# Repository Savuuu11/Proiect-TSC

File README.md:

# E-book Reader Open-Source
Savu Alin Ion 332CC

### Diagrama

---

### BOM - Bill of Materials

---

| Name of component | Device                                       | Check Prices                                                                                                                                | DataSheet                                                                                                                                   |
|-------------------|----------------------------------------------|---------------------------------------------------------------------------------------------------------------------------------------------|---------------------------------------------------------------------------------------------------------------------------------------------|
| BOOT_BUTTON       | BUTTON_CUSYOMV1                              | [Link](https://industry.panasonic.com/global/en/products/control/switch/light-touch/number/evqpuj02k)                                       | [Link](https://industry.panasonic.com/global/en/products/control/switch/light-touch/number/evqpuj02k)                                       |
| C1                | ESP32_WROVER_EAGLE-LTSPICE_CC0402            | [Link](https://industry.panasonic.com/global/en/products/control/switch/light-touch/number/evqpuj02k)                                       | [Link](https://industry.panasonic.com/global/en/products/control/switch/light-touch/number/evqpuj02k)                                       |
| C1_BAT            | ESP32_WROVER_EAGLE-LTSPICE_CC0402            | #N/A                                                                                                                                        | #N/A                                                                                                                                        |
| C1_BAT1           | EAGLE-LTSPICE_CC0402                         | #N/A                                                                                                                                        | #N/A                                                                                                                                        |
| C1_BAT2           | EAGLE-LTSPICE_CC0402                         | #N/A                                                                                                                                        | #N/A                                                                                                                                        |
| C2                | ESP32_WROVER_EAGLE-LTSPICE_CC0402            | #N/A                                                                                                                                        | #N/A                                                                                                                                        |
| C2_BAT\           | ESP32_WROVER_EAGLE-LTSPICE_CC0402            | #N/A                                                                                                                                        | #N/A                                                                                                                                        |
| C3                | RCL_CPOL-EUCT3528                            | #N/A                                                                                                                                        | #N/A                                                                                                                                        |
| C4                | ESP32_WROVER_EAGLE-LTSPICE_CC0402            | #N/A                                                                                                                                        | #N/A                                                                                                                                        |
| C4_USB            | ESP32_WROVER_EAGLE-LTSPICE_CC0402            | #N/A                                                                                                                                        | #N/A                                                                                                                                        |
| C5                | ESP32_WROVER_EAGLE-LTSPICE_CC0402            | #N/A                                                                                                                                        | #N/A                                                                                                                                        |
| C5_USB            | ESP32_WROVER_EAGLE-LTSPICE_CC0402            | #N/A                                                                                                                                        | #N/A                                                                                                                                        |
| C6                | ESP32_WROVER_EAGLE-LTSPICE_CC0402            | #N/A                                                                                                                                        | #N/A                                                                                                                                        |
| C7                | ESP32_WROVER_EAGLE-LTSPICE_CC0402            | #N/A                                                                                                                                        | #N/A                                                                                                                                        |
| C8                | ESP32_WROVER_EAGLE-LTSPICE_CC0402            | #N/A                                                                                                                                        | #N/A                                                                                                                                        |
| C9                | EAGLE-LTSPICE_CC0402                         | #N/A                                                                                                                                        | #N/A                                                                                                                                        |
| C10               | ESP32_WROVER_EAGLE-LTSPICE_CC0402            | #N/A                                                                                                                                        | #N/A                                                                                                                                        |
| C10_SUPERCAP      | CPH3225A                                     | [Link](https://www.snapeda.com/parts/CPH3225A/Seiko+Instruments/view-part/?ref=eda)                                                          | [Link](https://www.snapeda.com/parts/CPH3225A/Seiko+Instruments/view-part/?ref=eda)                                                          |
| CHANGE_BUTTON     | BUTTON_CUSYOMV1                              | [Link](https://industry.panasonic.com/global/en/products/control/switch-light-touch/number/evqpuj02k)                                       | [Link](https://industry.panasonic.com/global/en/products/control/switch-light-touch/number/evqpuj02k)                                       |
| CHG_LED           | ADAFRUIT_LEDCHIP-LED0603                     | [Link](https://www.snapeda.com/parts/KP-1608SURCK/Kingbright/view-part/?ref=search&t=LED%200603)                                             | [Link](https://www.snapeda.com/parts/KP-1608SURCK/Kingbright/view-part/?ref=search&t=LED%200603)                                             |
| C_DELAY           | ESP32_WROVER_EAGLE-LTSPICE_CC0402            | #N/A                                                                                                                                        | #N/A                                                                                                                                        |
| D1                | USBLC6-2SC6Y                                 | [Link](https://www.snapeda.com/parts/USBLC6-2SC6Y/STMicroelectronics/view-part/?ref=eda)                                                    | [Link](https://www.snapeda.com/parts/USBLC6-2SC6Y/STMicroelectronics/view-part/?ref=eda)                                                    |
| D2                | ESP32_WROVER_AVX---SD0805S020S1R0_AVX_...    | [Link](https://eu.mouser.com/ProductDetail/KYOCERA-AVX/SD0805S020S1R0?qs=jCA%252BPfw4LHbpkAoSnwrdjw%3D%3D)                                    | [Link](http://datasheets.avx.com/schottky.pdf)                                                                                              |
| D3                | MBR0530                                      | [Link](https://eu.mouser.com/ProductDetail/KYOCERA-AVX/SD0805S020S1R0?qs=jCA%252BPfw4LHbpkAoSnwrdjw%3D%3D)                                    | [Link](https://eu.mouser.com/ProductDetail/KYOCERA-AVX/SD0805S020S1R0?qs=jCA%252BPfw4LHbpkAoSnwrdjw%3D%3D)                                    |
| D4                | MBR0530                                      | [Link](https://www.snapeda.com/parts/MBR0530/Onsemi/view-part/?ref=eda)                                                                     | [Link](https://www.snapeda.com/parts/MBR0530/Onsemi/view-part/?ref=eda)                                                                     |
| D5                | MBR0530                                      | [Link](https://www.snapeda.com/parts/MBR0530/Onsemi/view-part/?ref=eda)                                                                     | [Link](https://www.snapeda.com/parts/MBR0530/Onsemi/view-part/?ref=eda)                                                                     |
| D6                | PGB1010603MR                                 | [Link](https://www.snapeda.com/parts/PGB1010603MR/Littelfuse/view-part/?ref=eda)                                                            | [Link](https://www.snapeda.com/parts/PGB1010603MR/Littelfuse/view-part/?ref=eda)                                                            |
| D7                | ESP32_WROVER_AVX---SD0805S020S1R0_AVX_...    | [Link](https://eu.mouser.com/ProductDetail/KYOCERA-AVX/SD0805S020S1R0?qs=jCA%252BPfw4LHbpkAoSnwrdjw%3D%3D)                                    | [Link](http://datasheets.avx.com/schottky.pdf)                                                                                              |
| D8                | PGB1010603MR                                 | [Link](https://www.snapeda.com/parts/PGB1010603MR/Littelfuse/view-part/?ref=eda)                                                            | [Link](https://www.snapeda.com/parts/PGB1010603MR/Littelfuse/view-part/?ref=eda)                                                            |
| D9                | PGB1010603MR                                 | [Link](https://www.snapeda.com/parts/PGB1010603MR/Littelfuse/view-part/?ref=eda)                                                            | [Link](https://www.snapeda.com/parts/PGB1010603MR/Littelfuse/view-part/?ref=eda)                                                            |
| D10               | PGB1010603MR                                 | [Link](https://www.snapeda.com/parts/PGB1010603MR/Littelfuse/view-part/?ref=eda)                                                            | [Link](https://www.snapeda.com/parts/PGB1010603MR/Littelfuse/view-part/?ref=eda)                                                            |
| D11               | PGB1010603MR                                 | [Link](https://www.snapeda.com/parts/PGB1010603MR/Littelfuse/view-part/?ref=eda)                                                            | [Link](https://www.snapeda.com/parts/PGB1010603MR/Littelfuse/view-part/?ref=eda)                                                            |
| D12               | PGB1010603MR                                 | [Link](https://www.snapeda.com/parts/PGB1010603MR/Littelfuse/view-part/?ref=eda)                                                            | [Link](https://www.snapeda.com/parts/PGB1010603MR/Littelfuse/view-part/?ref=eda)                                                            |
| EPD_C1            | ESP32_WROVER_EAGLE-LTSPICE_CC0402            | #N/A                                                                                                                                        | #N/A                                                                                                                                        |
| EPD_C2            | ESP32_WROVER_EAGLE-LTSPICE_CC0402            | #N/A                                                                                                                                        | #N/A                                                                                                                                        |
| EPD_C5            | ESP32_WROVER_EAGLE-LTSPICE_CC0402            | #N/A                                                                                                                                        | #N/A                                                                                                                                        |
| EPD_C6            | ESP32_WROVER_EAGLE-LTSPICE_CC0402            | #N/A                                                                                                                                        | #N/A                                                                                                                                        |
| EPD_C7            | ESP32_WROVER_EAGLE-LTSPICE_CC0402            | #N/A                                                                                                                                        | #N/A                                                                                                                                        |
| EPD_C8            | ESP32_WROVER_EAGLE-LTSPICE_CC0402            | #N/A                                                                                                                                        | #N/A                                                                                                                                        |
| EPD_C9            | ESP32_WROVER_EAGLE-LTSPICE_CC0402            | #N/A                                                                                                                                        | #N/A                                                                                                                                        |
| EPD_C10           | ESP32_WROVER_EAGLE-LTSPICE_CC0402            | #N/A                                                                                                                                        | #N/A                                                                                                                                        |
| EPD_C11           | ESP32_WROVER_EAGLE-LTSPICE_CC0402            | #N/A                                                                                                                                        | #N/A                                                                                                                                        |
| EPD_C12           | ESP32_WROVER_EAGLE-LTSPICE_CC0402            | #N/A                                                                                                                                        | #N/A                                                                                                                                        |
| IC1               | BD5229G-TR                                   | [Link](https://componentsearchengine.com/part-view/BD5229G-TR/ROHM%20Semiconductor)                                                         | [Link](https://componentsearchengine.com/part-view/BD5229G-TR/ROHM%20Semiconductor)                                                         |
| IC4               | XC6220A331MR-G                               | [Link](https://componentsearchengine.com/part-view/XC6220A331MR-G/Torex)                                                                     | [Link](https://componentsearchengine.com/part-view/XC6220A331MR-G/Torex)                                                                     |
| J1                | FH34SRJ-24S-0.5SH_99_                        | [Link](https://componentsearchengine.com/part-view/XC6220A331MR-G/Torex)                                                                     | [Link](https://componentsearchengine.com/part-view/XC6220A331MR-G/Torex)                                                                     |
| J2                | SAMACSYS_PARTS_USB4110-GF-A                  | [Link](https://componentsearchengine.com/part-view/USB4110-GF-A/GCT%20(GLOBAL%20CONNECTOR%20TECHNOLOGY)                                      | [Link](https://componentsearchengine.com/part-view/USB4110-GF-A/GCT%20(GLOBAL%20CONNECTOR%20TECHNOLOGY)                                      |
| J3                | QWIIC_CONNECTORJS-1MM                        | #N/A                                                                                                                                        | #N/A                                                                                                                                        |
| J4                | 112A-TAAR-R03_ATTEND                         | [Link](https://store.comet.srl.ro/Catalogue/Product/43497/)                                                                                | [Link](https://store.comet.srl.ro/Catalogue/Product/43497/)                                                                                |
| L1                | 744043680IND_4828-WE-TPC_WRE                 | [Link](https://eu.mouser.com/ProductDetail/Wurth-Elektronik/744043680?qs=PGXP4M47uW6VkZq%252BkzjrHA%3D%3D)                                    | [Link](https://eu.mouser.com/ProductDetail/Wurth-Elektronik/744043680?qs=PGXP4M47uW6VkZq%252BkzjrHA%3D%3D)                                    |
| PFMF.050.1        | ESP32C6_VARISTORCN1812                       | [Link](https://www.mouser.co.uk/ProductDetail/EPCOS-TDK/B72520T0350K062?qs=dEfas%2FXlABIszF52uu7vrg%3D%3D)                                  | [Link](https://www.mouser.co.uk/ProductDetail/EPCOS-TDK/B72520T0350K062?qs=dEfas%2FXlABIszF52uu7vrg%3D%3D)                                  |
| Q1                | ESP32_WROVER_SPARKFUN-DISCRETESEMI_MOSFET_...| [Link](https://componentsearchengine.com/part-view/DMG2305UX-7/Diodes%20Incorporated)                                                       | [Link](https://componentsearchengine.com/part-view/DMG2305UX-7/Diodes%20Incorporated)                                                       |
| Q2                | ESP32_WROVER_SPARKFUN-DISCRETESEMI_MOSFET_...| #N/A                                                                                                                                        | #N/A                                                                                                                                        |
| Q3                | D8                                           | [Link](https://componentsearchengine.com/part-view/SI1308EDL-T1-GE3/Vishay)                                                                 | [Link](https://componentsearchengine.com/part-view/SI1308EDL-T1-GE3/Vishay)                                                                 |
| R1                | ESP32_WROVER_EAGLE-LTSPICE_RR0402            | #N/A                                                                                                                                        | #N/A                                                                                                                                        |
| R1-PINH           | ESP32_WROVER_EAGLE-LTSPICE_RR0402            | #N/A                                                                                                                                        | #N/A                                                                                                                                        |
| R1-PINH1          | ESP32_WROVER_EAGLE-LTSPICE_RR0402            | #N/A                                                                                                                                        | #N/A                                                                                                                                        |
| R1_BAT            | ESP32_WROVER_EAGLE-LTSPICE_RR0402            | #N/A                                                                                                                                        | #N/A                                                                                                                                        |
| R1_PWRUSB         | ESP32_WROVER_EAGLE-LTSPICE_RR0402            | #N/A                                                                                                                                        | #N/A                                                                                                                                        |
| R2                | ESP32_WROVER_EAGLE-LTSPICE_RR0402            | [Link](https://componentsearchengine.com/part-view/R0402%201%25%20100%20K%20(RC0402FR-07100KL)                                               | [Link](https://componentsearchengine.com/part-view/R0402%201%25%20100%20K%20(RC0402FR-07100KL)                                               |
| R2-PINH           | ESP32_WROVER_EAGLE-LTSPICE_RR0402            | #N/A                                                                                                                                        | #N/A                                                                                                                                        |
| R2-PINH1          | ESP32_WROVER_EAGLE-LTSPICE_RR0402            | #N/A                                                                                                                                        | #N/A                                                                                                                                        |
| R2-USB            | ESP32_WROVER_EAGLE-LTSPICE_RR0402            | #N/A                                                                                                                                        | #N/A                                                                                                                                        |
| R2-USB1           | ESP32_WROVER_EAGLE-LTSPICE_RR0402            | #N/A                                                                                                                                        | #N/A                                                                                                                                        |
| R2_BAT            | ESP32_WROVER_EAGLE-LTSPICE_RR0402            | #N/A                                                                                                                                        | #N/A                                                                                                                                        |
| R3                | ESP32_WROVER_EAGLE-LTSPICE_RR0402            | #N/A                                                                                                                                        | #N/A                                                                                                                                        |
| R4                | ESP32_WROVER_EAGLE-LTSPICE_RR0402            | #N/A                                                                                                                                        | #N/A                                                                                                                                        |
| R5                | ESP32_WROVER_EAGLE-LTSPICE_RR0402            | #N/A                                                                                                                                        | #N/A                                                                                                                                        |
| R6                | ESP32_WROVER_EAGLE-LTSPICE_RR0402            | #N/A                                                                                                                                        | #N/A                                                                                                                                        |
| R7                | ESP32_WROVER_EAGLE-LTSPICE_RR0402            | #N/A                                                                                                                                        | #N/A                                                                                                                                        |
| R8                | ESP32_WROVER_EAGLE-LTSPICE_RR0402            | #N/A                                                                                                                                        | #N/A                                                                                                                                        |
| R9                | ESP32_WROVER_EAGLE-LTSPICE_RR0402            | #N/A                                                                                                                                        | #N/A                                                                                                                                        |
| R10               | ESP32_WROVER_EAGLE-LTSPICE_RR0402            | #N/A                                                                                                                                        | #N/A                                                                                                                                        |
| RESET_BUTTON      | BUTTON_CUSYOMV1                              | [Link](https://industry.panasonic.com/global/en/products/control/switch/light-touch/number/evqpuj02k)                                       | [Link](https://industry.panasonic.com/global/en/products/control/switch/light-touch/number/evqpuj02k)                                       |
| R_BOOT            | ESP32_WROVER_EAGLE-LTSPICE_RR0402            | #N/A                                                                                                                                        | #N/A                                                                                                                                        |
| R_CAPACITOR       | ESP32_WROVER_EAGLE-LTSPICE_RR0402            | #N/A                                                                                                                                        | #N/A                                                                                                                                        |
| R_CHANGE          | ESP32_WROVER_EAGLE-LTSPICE_RR0402            | #N/A                                                                                                                                        | #N/A                                                                                                                                        |
| R_CL1             | ESP32_WROVER_EAGLE-LTSPICE_RR0402            | #N/A                                                                                                                                        | #N/A                                                                                                                                        |
| R_RESET           | ESP32_WROVER_EAGLE-LTSPICE_RR0402            | #N/A                                                                                                                                        | #N/A                                                                                                                                        |
| SENSOR2           | ESP32_WROVER_BME680_BME680                   | [Link](https://www.snapeda.com/parts/BME680/Bosch/view-part/?welcome=home)                                                                  | [Link](https://www.snapeda.com/parts/BME680/Bosch/view-part/?welcome=home)                                                                  |
| SJ1               | SJ                                           | [Link](https://grabcad.com/library/solder-jumpers-1)                                                                                        | [Link](https://grabcad.com/library/solder-jumpers-1)                                                                                        |
| TP1               | TPTP20R                                      | #N/A                                                                                                                                        | #N/A                                                                                                                                        |
| TP2               | TPTP20R                                      | #N/A                                                                                                                                        | #N/A                                                                                                                                        |
| TP3               | TPTP20R                                      | #N/A                                                                                                                                        | #N/A                                                                                                                                        |
| TP4               | TPTP20R                                      | #N/A                                                                                                                                        | #N/A                                                                                                                                        |
| TP5               | TPTP20R                                      | #N/A                                                                                                                                        | #N/A                                                                                                                                        |
| TP6               | TPTP20R                                      | #N/A                                                                                                                                        | #N/A                                                                                                                                        |
| TP7               | TPTP20R                                      | #N/A                                                                                                                                        | #N/A                                                                                                                                        |
| TP8               | TPTP20R                                      | #N/A                                                                                                                                        | #N/A                                                                                                                                        |
| TP9               | TPTP20R                                      | #N/A                                                                                                                                        | #N/A                                                                                                                                        |
| TP10              | TPTP20R                                      | #N/A                                                                                                                                        | #N/A                                                                                                                                        |
| TP11              | TPTP20R                                      | #N/A                                                                                                                                        | #N/A                                                                                                                                        |
| TP12              | TPTP20R                                      | #N/A                                                                                                                                        | #N/A                                                                                                                                        |
| TP13              | TPTP20R                                      | #N/A                                                                                                                                        | #N/A                                                                                                                                        |
| TP14              | TPTP20R                                      | #N/A                                                                                                                                        | #N/A                                                                                                                                        |
| TP15              | TPTP20R                                      | #N/A                                                                                                                                        | #N/A                                                                                                                                        |
| TP16              | TPTP20R                                      | #N/A                                                                                                                                        | #N/A                                                                                                                                        |
| TP17              | TPTP20R                                      | #N/A                                                                                                                                        | #N/A                                                                                                                                        |
| U1                | W25Q512JVEIQ                                 | [Link](https://www.snapeda.com/parts/W25Q512JVEIQ/Winbond+Electronics/view-part/?ref=eda)                                                    | [Link](https://www.snapeda.com/parts/W25Q512JVEIQ/Winbond+Electronics/view-part/?ref=eda)                                                    |
| U2                | ESP32-C6-WROOM-1-N8                          | [Link](https://www.snapeda.com/parts/ESP32-C6-WROOM-1-N8/Espressif+Systems/view-part/?ref=eda)                                              | [Link](https://www.snapeda.com/parts/ESP32-C6-WROOM-1-N8/Espressif+Systems/view-part/?ref=eda)                                              |
| U3                | DS3231SN#                                    | [Link](https://www.snapeda.com/parts/DS3231SN%23/Analog+Devices/view-part/?ref=eda)                                                         | [Link](https://www.snapeda.com/parts/DS3231SN%23/Analog+Devices/view-part/?ref=eda)                                                         |
| U4                | MAX17048G+T10                                | [Link](https://www.snapeda.com/parts/MAX17048G+T10/Analog+Devices/view-part/?ref=eda)                                                       | [Link](https://www.snapeda.com/parts/MAX17048G+T10/Analog+Devices/view-part/?ref=eda)                                                       |
| U5                | ESP32_WROVER_SPARKFUN-IC-POWER_MCP73831      | [Link](https://eu.mouser.com/ProductDetail/Microchip-Technology/MCP73831T-2ACI-OT?qs=yUQqVecv4qvbBQBGbHx0Mw%3D%3Dcf)                         | [Link](https://eu.mouser.com/ProductDetail/Microchip-Technology/MCP73831T-2ACI-OT?qs=yUQqVecv4qvbBQBGbHx0Mw%3D%3Dcf)                         |

## Descriere Funcționalități Hardware

---

## 1. Unitate de Control – ESP32-C6  
- **Microcontroller**: `ESP32-C6-WROOM-1` (32-bit RISC-V @ 160 MHz)  
- **Memorie**:  
  - 512 KB SRAM integrat pentru procesare rapidă.  
  - 8 MB flash extern (`W25Q512JVEIQ`) pentru stocare persistentă.  
- **Conectivitate**:  
  - Wi-Fi 6 (802.11ax), Bluetooth Low Energy 5.  
  - Port USB 2.0 (full-speed).  
- **Periferice**:  
  - SPI, I²C, UART.  
  - 22 de pini GPIO configurabili.  
- **Eficiență energetică**:  
  - Moduri `sleep` și `deep sleep` (<10µA).  

---

## 2. Afișaj E-Ink (7.5 inch)  
- **Model**: Waveshare 800×480 px.  
- **Interfață**:  
  - SPI 4-fire (CS, DC, RST, BUSY).  
- **Consum energie**:  
  - **0W** în stare statică.  
  - Vârf de **25mA** la actualizare.  
- **Beneficiu**:  
  - Imagine persistentă fără alimentare.  

---

## 3. Senzor Multi-Parametru – BME680  
- **Măsurători**:  
  - Temperatură (±0.5°C), umiditate (±3%), presiune atmosferică, VOC.  
- **Interfață**: I²C @ 400 kHz.  
- **Consum**:  
  - 2.1µA în standby, 3.7mA în activitate.  
- **Avantaj**: Integrare 4-în-1 într-un singur cip.  

---

## 4. Sistem de Management al Energiei  
- **Baterie**: Li-Po 2500mAh (3.7V).  
- **Încărcare**:  
  - Controler `MCP73831` (1A via USB-C).  
- **Monitorizare**:  
  - `MAX17048` pentru nivel încărcare, tensiune și alertă.  
- **Regulator LDO**:  
  - `XC6220A331MR-G` (3.3V stabil).  

---

## 5. Interfață Utilizator – Butoane Tactile  
- **3 butoane** pentru navigare, selecție și control.  
- **Debouncing**:  
  - Hardware (circuite RC) sau software.  

---

## 6. Port USB-C  
- **Funcții**:  
  - Încărcare baterie și transfer date.  
- **Protecție**:  
  - Diodă ESD `USBLC6-2SC6Y`.  

---

## 7. Conector Qwiic pentru Expansiune  
- **4 pini standard**: VCC, GND, SDA, SCL.  
- **Scop**: Conectare senzori I²C externi (ex: senzor de lumină).  

---

## 8. Slot MicroSD  
- **Conector**: `112A-TAAR-R03`.  
- **Capacitate**: Suportă carduri microSD (stocare e-book-uri/log-uri).  
- **Interfață**: Configurabilă SPI/SD.  

---

## 9. Ceas Real-Time (DS3231)  
- **Precizie**: ±2ppm.  
- **Backup**: Supercondensator/baterie secundară.  

---

## 10. Memorie Flash Externă  
- **Model**: `W25Q512JVEIQ`.  
- **Interfață**: Quad SPI (133 MHz).  
- **Utilizare**: Firmware, setări, conținut utilizator.  

--- 

### 🔌 Interfețe și Alocare Resurse  

#### **Interfețe Utilizate**  
| Protocol | Componente Conectate               |  
|----------|------------------------------------|  
| **SPI**  | E-Paper, Memorie Flash, Card SD    |  
| **I²C**  | BME680, MAX17048, DS3231, Qwiic    |  
| **GPIO** | Butoane, Semnale Control E-Paper   |  
| **USB**  | Alimentare + Transfer Date (USB-C) |  

---

#### **Estimare Autonomie Baterie**  
| Componentă             | Consum (Activ) | Consum (Standby) |  
|------------------------|----------------|------------------|  
| **ESP32-C6**           | 80 mA          | <10 µA           |  
| **E-Paper (refresh)**  | 25 mA          | 0 mA             |  
| **BME680**             | 3.6 mA         | 2.1 µA           |  
| **MAX17048**           | -              | 50 µA            |  
| **DS3231**             | 3.5 mA         | <1 µA            |  
| **Total**              | ~150 mA        | ~100 µA          |  

---

#### **Mapare Pini ESP32-C6**  
| Pin   | Funcție Principală                 | Detalii                          |  
|-------|------------------------------------|----------------------------------|  
| GPIO1 | I²C SDA                            | Senzori BME680, MAX17048, DS3231 |  
| GPIO2 | I²C SCL                            | Clock pentru magistrala I²C      |  
| GPIO5 | SPI MISO (E-Paper)                 | Recepție date afișaj             |  
| GPIO6 | SPI MOSI (E-Paper)                 | Transmitere date afișaj          |  
| GPIO7 | SPI CLK (E-Paper)                  | Semnal ceas SPI                  |  
| GPIO8 | SPI CS (E-Paper)                   | Selectare chip afișaj            |  
| GPIO9 | DC (E-Paper)                       | Comutare date/comenzi            |  
| GPIO10| RST (E-Paper)                      | Reset hardware afișaj            |  
| GPIO11| BUSY (E-Paper)                     | Indică ocupare afișaj            |  
| GPIO12| Buton #1                           | Navigare "Pagina Următoare"      |  
| GPIO13| Buton #2                           | Navigare "Pagina Anterioară"     |  
| GPIO14| Buton #3                           | Meniu/Selectare                  |  
| GPIO15| ALERT (MAX17048)                   | Avertizare baterie scăzută       |  
| GPIO19| SD Card CS                         | Selectare card MicroSD           |  

---

### Conluzii
A fost un proiect foarte muncitoresc, care merita mai mult decat 2 pct.
Timp de lucru: 70h

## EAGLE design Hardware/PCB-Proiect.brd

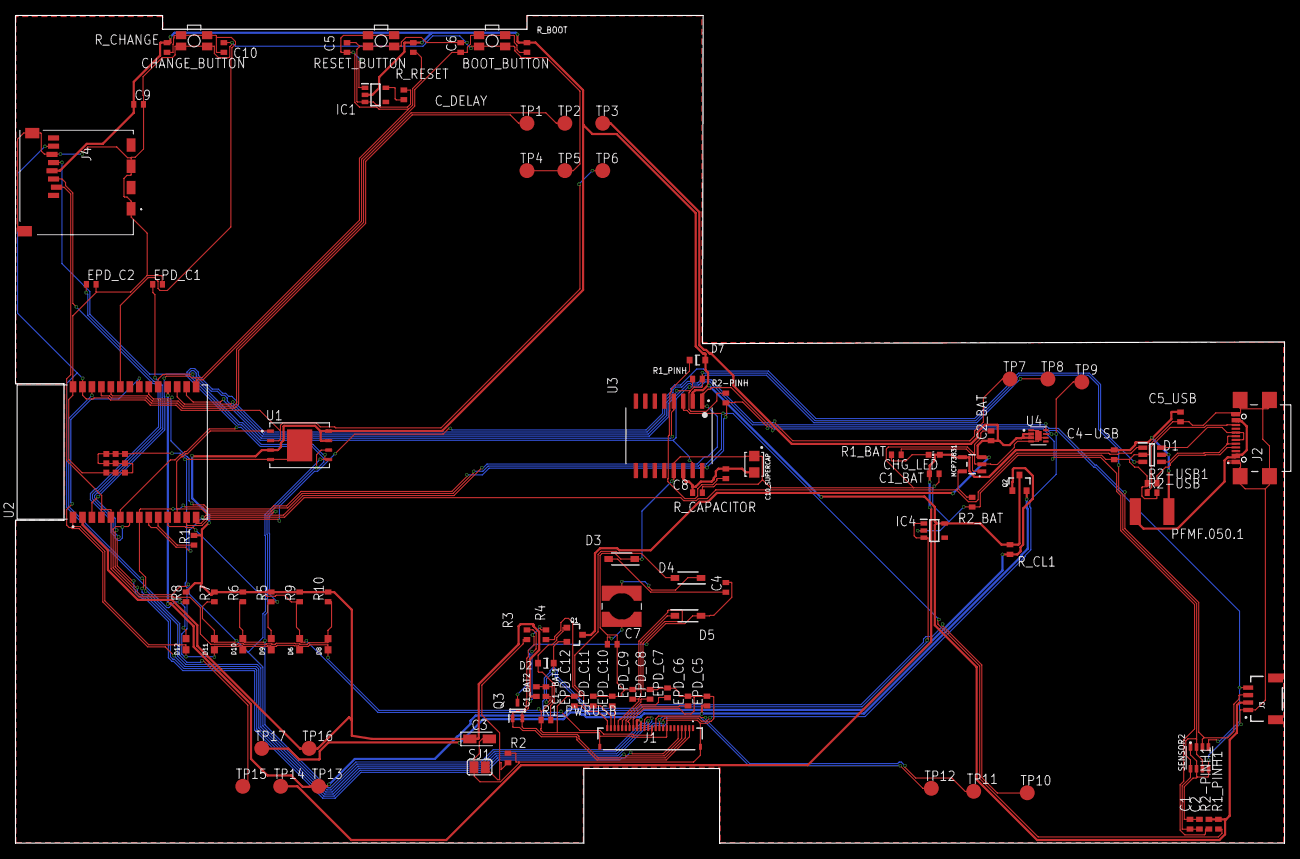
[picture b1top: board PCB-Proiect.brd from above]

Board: 2 copper layers, 170.2 x 111.0 mm, 103 parts (0 on the bottom side), 58 nets.

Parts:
BOOT_BUTTON: BUTTON_CUSYOMV1; MYBUTTON
C1, C2, C6, C8, C9, C10: 100nF; EAGLE-LTSPICE_C0402
C1-BAT1, C1_BAT2, C5_USB: 4.7uF; ESP32_WROVER_EAGLE-LTSPICE_C0402
C1_BAT, C2_BAT: 4.7uF; EAGLE-LTSPICE_C0402
C3: 100uF TANT; CAPMP3216X180N
C4: 4.7uF/25V; EAGLE-LTSPICE_C0402
C4-USB: 100nF; ESP32_WROVER_EAGLE-LTSPICE_C0402
C5: 1uF; EAGLE-LTSPICE_C0402
C7: 10uF; EAGLE-LTSPICE_C0402
C10_SUPERCAP: CPH3225A; CAPCP3225X100N
CHANGE_BUTTON: BUTTON_CUSYOMV1; MYBUTTON
CHG_LED: ADAFRUIT_CHIP-LED0603
C_DELAY: 100nF; EAGLE-LTSPICE_C0402
D1: USBLC6-2SC6Y; SOT95P280X145-6N
D2, D7: ESP32_WROVER_AVX---SD0805S020S1R0_AVX_SD0805S020S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; ESP32_WROVER_AVX---SD0805S020S1R0_AVX_SD0805S020S1R0_0
D3, D4, D5: MBR0530; SOD3716X135N
D6, D8, D9, D10, D11, D12: PGB1010603MR; DIOC1608X36N
EPD_C1, EPD_C2, EPD_C5, EPD_C6, EPD_C7, EPD_C8, EPD_C9, EPD_C10, EPD_C11, EPD_C12: 1uF/50V; EAGLE-LTSPICE_C0402
IC1: BD5229G-TR; SOT95P280X125-5N
IC4: XC6220A331MR-G; SOT95P280X120-5N
J1: FH34SRJ-24S-0.5SH_99_; FH34SRJ24S05SH99
J2: SAMACSYS_PARTS_USB4110-GF-A; SAMACSYS_PARTS_USB4110GFA
J3: QWIIC_RIGHT_ANGLE; JST04_1MM_RA
J4: 112A-TAAR-R03_ATTEND; 112ATAARR03ATTEND
L1: 68uH; IND_4828-WE-TPC_WRE
MCP73831: ESP32_WROVER_SPARKFUN-IC-POWER_MCP73831; ESP32_WROVER_SPARKFUN-IC-POWER_SOT23-5
PFMF.050.1: ESP32C6_VARISTORCN1812; ESP32C6_VARISTOR_CT/CN1812
Q1, Q2: 20V/4.2A/52mΩ/1.4W; ESP32_WROVER_SPARKFUN-DISCRETESEMI_SOT23-3
Q3: SI1308EDL-T1-GE3; SOT65P210X110-3N
R1, R1_PINH, R1_PINH1, R2-PINH, R2-PINH1, R4, R5, R6, R7, R8, R9, R10: 10K; ESP32_WROVER_EAGLE-LTSPICE_R0402
R1_BAT: 200; ESP32_WROVER_EAGLE-LTSPICE_R0402
R1_PWRUSB: 100K; ESP32_WROVER_EAGLE-LTSPICE_R0402
R2: 2.2; ESP32_WROVER_EAGLE-LTSPICE_R0402
R2-USB, R2-USB1: 5k1; ESP32_WROVER_EAGLE-LTSPICE_R0402
R2_BAT: 2K; ESP32_WROVER_EAGLE-LTSPICE_R0402
R3: 0.47; ESP32_WROVER_EAGLE-LTSPICE_R0402
RESET_BUTTON: BUTTON_CUSYOMV1; MYBUTTON
R_BOOT: 10K; ESP32_WROVER_EAGLE-LTSPICE_R0402
R_CAPACITOR: 15; ESP32_WROVER_EAGLE-LTSPICE_R0402
R_CHANGE: 10K; ESP32_WROVER_EAGLE-LTSPICE_R0402
R_CL1: 10K; ESP32_WROVER_EAGLE-LTSPICE_R0402
R_RESET: 10K; ESP32_WROVER_EAGLE-LTSPICE_R0402
SENSOR2: ESP32_WROVER_BME680_BME680; ESP32_WROVER_BME680_PSON80P300X300X100-8N
SJ1: SJ
TP1, TP2, TP3, TP4, TP5, TP6, TP7, TP8, TP9, TP10, TP11, TP12, TP13, TP14, TP15, TP16, TP17: TPTP20R; TP20R
U1: W25Q512JVEIQ; SON127P600X800X80-9N
U2: ESP32-C6-WROOM-1-N8; XCVR_ESP32-C6-WROOM-1-N8
U3: DS3231SN#; SOIC127P1032X265-16N
U4: MAX17048G+T10; SON50P200X200X80-9N

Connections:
3V3: C1_BAT2.1, C3.1, C9.1, D7.2, IC1.2, IC4.5, J3.2, J4.P4, Q2.3, R1.2, R1_PINH1.2, R2-PINH1.2, R5.2, R6.2, R7.2, R8.2, R9.2, R10.2, R_BOOT.2, R_CHANGE.2, R_CL1.2, R_RESET.2, TP16.TP, U1.3, U1.7, U1.8, U2.2, U3.2
32KHZ: R2-PINH1.1, U2.9, U3.1
DN: D1.4, J2.A7, J2.B7
DP: D1.6, J2.A6, J2.B6
EPD_3V3: EPD_C5.1, J1.15, J1.16, Q2.2, TP17.TP
EPD_3V3_C: Q2.1, R_CL1.1, TP13.TP, U2.18
EPD_BUSY: J1.9, TP9.TP, U2.26
EPD_CS: D6.2, J1.12, R9.1, TP10.TP, U2.11
EPD_DC: J1.11, TP11.TP
EPD_RST: J1.10, TP12.TP, U2.21
FLASH_CS: D9.2, R5.1, U1.1, U2.12
GDR: J1.2, Q3.1, R4.2
GND: BOOT_BUTTON.1, BOOT_BUTTON.2, C1.2, C1-BAT1.2, C1_BAT.2, C1_BAT2.2, C2.2, C2_BAT.2, C3.2, C4-USB.1, C5.2, C5_USB.1, C6.2, C7.2, C8.2, C9.2, C10.2, C10_SUPERCAP.1, CHANGE_BUTTON.1, CHANGE_BUTTON.2, C_DELAY.2, D1.2, D3.1, D6.1, D8.1, D9.1, D10.1, D11.1, D12.1, EPD_C1.2, EPD_C2.2, EPD_C5.2, EPD_C6.2, EPD_C7.2, EPD_C8.2, EPD_C9.2, EPD_C10.2, EPD_C11.2, EPD_C12.2, IC1.3, IC4.2, J1.8, J1.17, J1.MP1, J1.MP2, J2.A1, J2.A12, J2.B1, J2.B12, J2.MP1, J2.MP2, J2.MP3, J2.MP4, J3.1, J4.G1, J4.G2, J4.G3, J4.G4, J4.P6, MCP73831.2, R1_PWRUSB.1, R2.2, R2-USB.2, R2-USB1.1, R2_BAT.1, R4.1, RESET_BUTTON.1, RESET_BUTTON.2, SENSOR2.1, SENSOR2.5, SENSOR2.7, SJ1.1, TP4.TP, TP5.TP, U1.4, U1.9, U2.1, U2.28, U2.29_1, U2.29_2, U2.29_3, U2.29_4, U2.29_5, U2.29_6, U2.29_7, U2.29_8, U2.29_9, U3.13, U4.1, U4.4, U4.6, U4.9
GPI08: R1.1, U2.10
I2C_PW: C1.1, C2.1, R1_PINH.2, R2-PINH.2, SENSOR2.2, SENSOR2.6, SENSOR2.8, U2.17
INT_RTC: R1_PINH1.1, TP15.TP, U2.8, U3.3
IO/BOOT: BOOT_BUTTON.3, BOOT_BUTTON.4, C6.1, R_BOOT.1, U2.15
IO/CHANGE: C10.1, CHANGE_BUTTON.3, CHANGE_BUTTON.4, R_CHANGE.1, U2.23
MISO: D12.2, J4.P7, R8.1, TP6.TP, U1.2, U2.27
MOSI: D11.2, J1.14, J4.P3, R7.1, TP7.TP, U1.5, U2.7
unnamed: D2.2, Q1.1, R1_PWRUSB.2
unnamed: J2.B5, R2-USB.1
unnamed: J2.A5, R2-USB1.2
unnamed: C7.1, L1.2
unnamed: C1-BAT1.1, D2.1, IC4.1, IC4.3, Q1.2
unnamed: D4.1, L1.1
unnamed: C4.1, D3.2
unnamed: CHG_LED.C, R1_BAT.1
unnamed: MCP73831.1, R1_BAT.2
unnamed: MCP73831.5, R2_BAT.2
unnamed: C_DELAY.1, IC1.5
unnamed: EPD_C12.1, J1.24
unnamed: EPD_C10.1, J1.22
unnamed: EPD_C8.1, J1.20
unnamed: EPD_C7.1, J1.19
unnamed: D7.1, R_CAPACITOR.1
unnamed: EPD_C6.1, J1.18
unnamed: EPD_C2.1, J1.5
unnamed: EPD_C1.1, J1.4
PREVGH: D5.1, EPD_C9.1, J1.21
PREVGL: D4.2, EPD_C11.1, J1.23
RESE: J1.3, Q3.2, R3.2
RESE': R2.1, R3.1, SJ1.2
RESET: C5.1, IC1.1, RESET_BUTTON.3, RESET_BUTTON.4, R_RESET.1, U2.3
RTC_RST: U2.16, U3.4
RX: TP2.TP, U2.24
SCK: D10.2, J1.13, J4.P5, R6.1, TP8.TP, U1.6, U2.6
SCL: J3.4, R2-PINH.1, SENSOR2.4, U2.20, U3.16, U4.7
SDA: J3.3, R1_PINH.1, SENSOR2.3, U2.19, U3.15, U4.8
SRC: C4.2, D5.2, Q3.3
SS_SD: D8.2, J4.P2, R10.1, U2.4, U2.5
TX: TP1.TP, U2.25
USB_D+: D1.1, U2.14
USB_D-: D1.3, U2.13
VBAT: C2_BAT.1, MCP73831.3, Q1.3, TP3.TP, U4.2, U4.3
VBUS: C1_BAT.1, C4-USB.2, C5_USB.2, CHG_LED.A, D1.5, MCP73831.4, PFMF.050.1.2, TP14.TP
VRTC: C8.1, C10_SUPERCAP.2, R_CAPACITOR.2, U3.14
VUSB: J2.A4, J2.A9, J2.B4, J2.B9, PFMF.050.1.1

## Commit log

2025-04-06 Create ASDA
2025-04-06 Create ASFAD
2025-04-06 Create sadfsg
2025-04-06 Create LICENSE
2025-04-06 Create ASDFS
2025-04-14 Create SFD
2025-04-14 Create SDAFS

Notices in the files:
parts and their libraries:
COPYRIGHT: Copyright (C) 2024 Ultra Librarian. All rights reserved.
